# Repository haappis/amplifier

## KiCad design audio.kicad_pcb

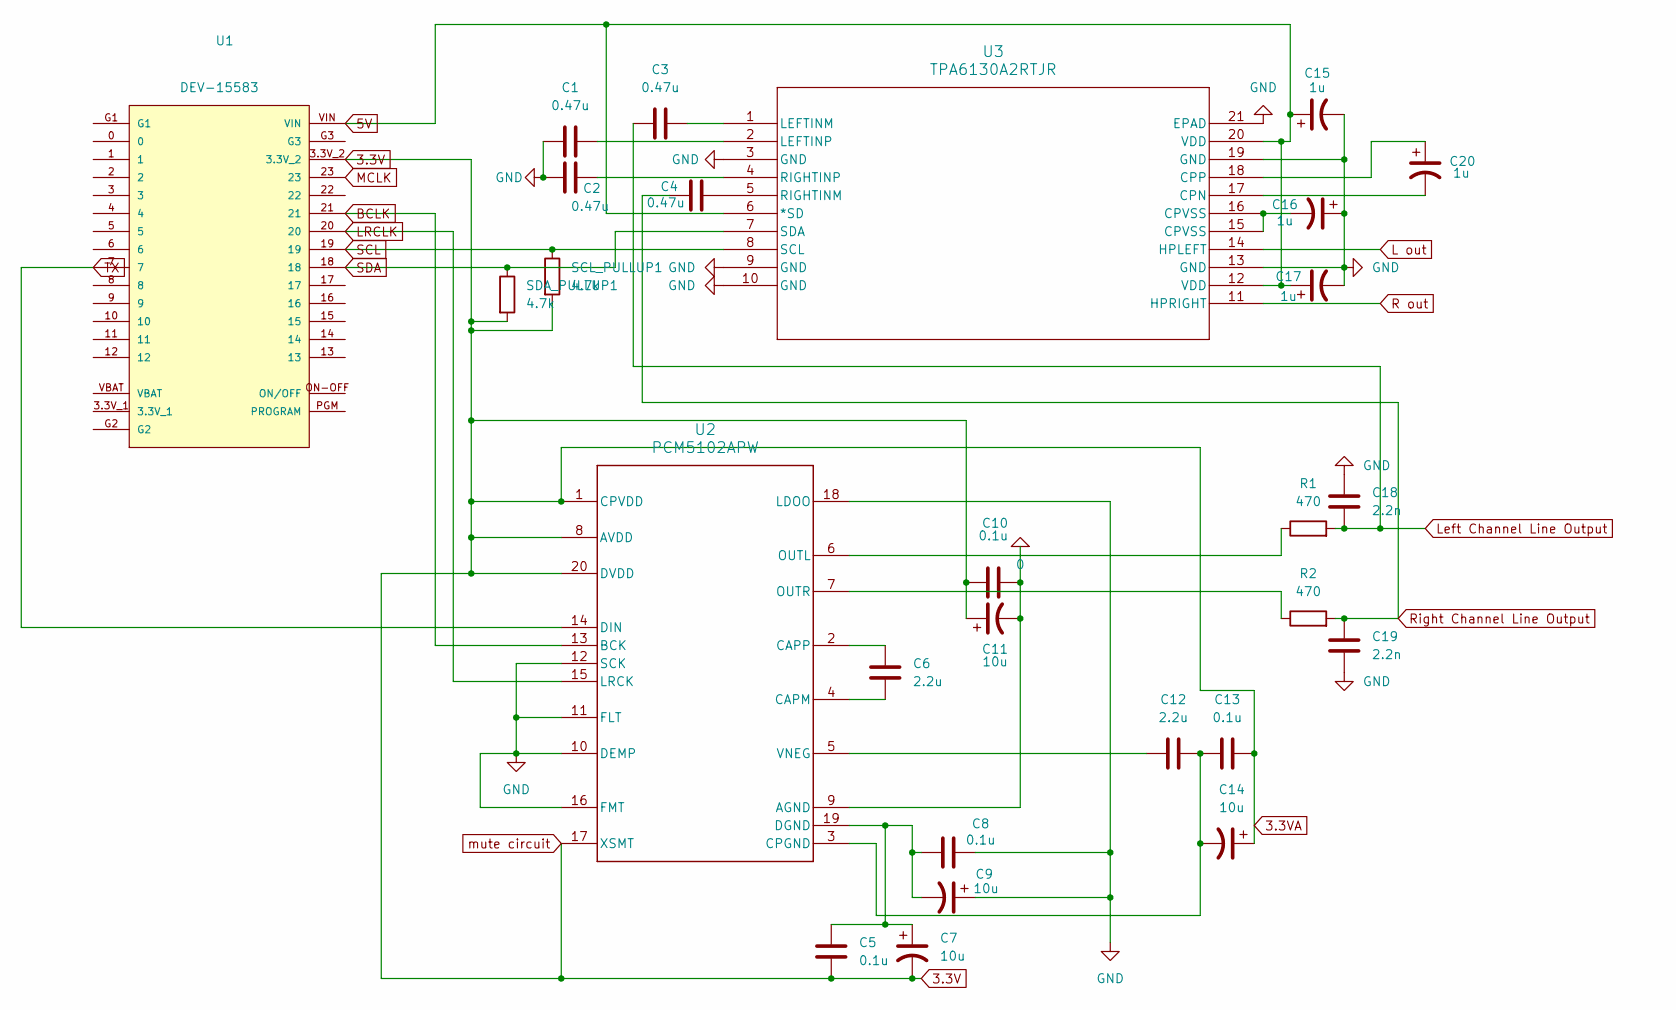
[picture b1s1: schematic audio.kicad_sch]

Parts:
C1, C2, C3, C4: 0.47u; C_0504_1310Metric
C5, C8, C10: 0.1u; C_0805_2012Metric
C6, C12: 2.2u; C_0504_1310Metric
C7, C9, C11: 10u; C_0805_2012Metric
C13: 0.1u; C_0504_1310Metric
C14: 10u; C_0504_1310Metric
C15, C16, C17, C20: 1u; C_0504_1310Metric
C18, C19: 2.2n; C_0504_1310Metric
R1, R2: 470; R_0805_2012Metric
SCL_PULLUP1: 4.7k; R_0805_2012Metric
SDA_PULLUP1: 4.7k; R_0805_2012Metric
U1: DEV-15583; MODULE_DEV-15583
U2: PCM5102APW; PW0020A_N
U3: TPA6130A2RTJR; RTJ20_2P7X2P7

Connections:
3.3V: C5.2, C7.2, C10.1, C11.1, C13.2, C14.1, SCL_PULLUP1.2, SDA_PULLUP1.2, U1.3.3V_2, U2.1 (CPVDD), U2.8 (AVDD), U2.17 (XSMT), U2.20 (DVDD); also elsewhere on the board
5V: C15.1, C17.1, U1.VIN, U3.6 (*SD), U3.12 (VDD), U3.20 (VDD); also elsewhere on the board
BCLK: U1.21, U2.13 (BCK); also elsewhere on the board
L out: U3.14 (HPLEFT); also elsewhere on the board
LRCLK: U1.20, U2.15 (LRCK); also elsewhere on the board
Left Channel Line Output: C3.1, C18.2, R1.2
unnamed: C16.2, U3.15 (CPVSS), U3.16 (CPVSS)
unnamed: C6.2, U2.4 (CAPM)
unnamed: C6.1, U2.2 (CAPP)
unnamed: C12.2, C13.1, C14.2, U2.3 (CPGND)
unnamed: C5.1, C7.1, C8.1, C9.2, U2.19 (DGND)
unnamed: R1.1, U2.6 (OUTL)
unnamed: R2.1, U2.7 (OUTR)
unnamed: C12.1, U2.5 (VNEG)
unnamed: C20.2, U3.17 (CPN)
unnamed: C20.1, U3.18 (CPP)
unnamed: C3.2, U3.1 (LEFTINM)
unnamed: C1.2, U3.2 (LEFTINP)
unnamed: C4.2, U3.5 (RIGHTINM)
unnamed: C2.2, U3.4 (RIGHTINP)
R out: U3.11 (HPRIGHT); also elsewhere on the board
Right Channel Line Output: C4.1, C19.1, R2.2
SCL: SCL_PULLUP1.1, U1.19, U3.8 (SCL); also elsewhere on the board
SDA: SDA_PULLUP1.1, U1.18, U3.7 (SDA); also elsewhere on the board
TX: U1.7, U2.14 (DIN); also elsewhere on the board

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
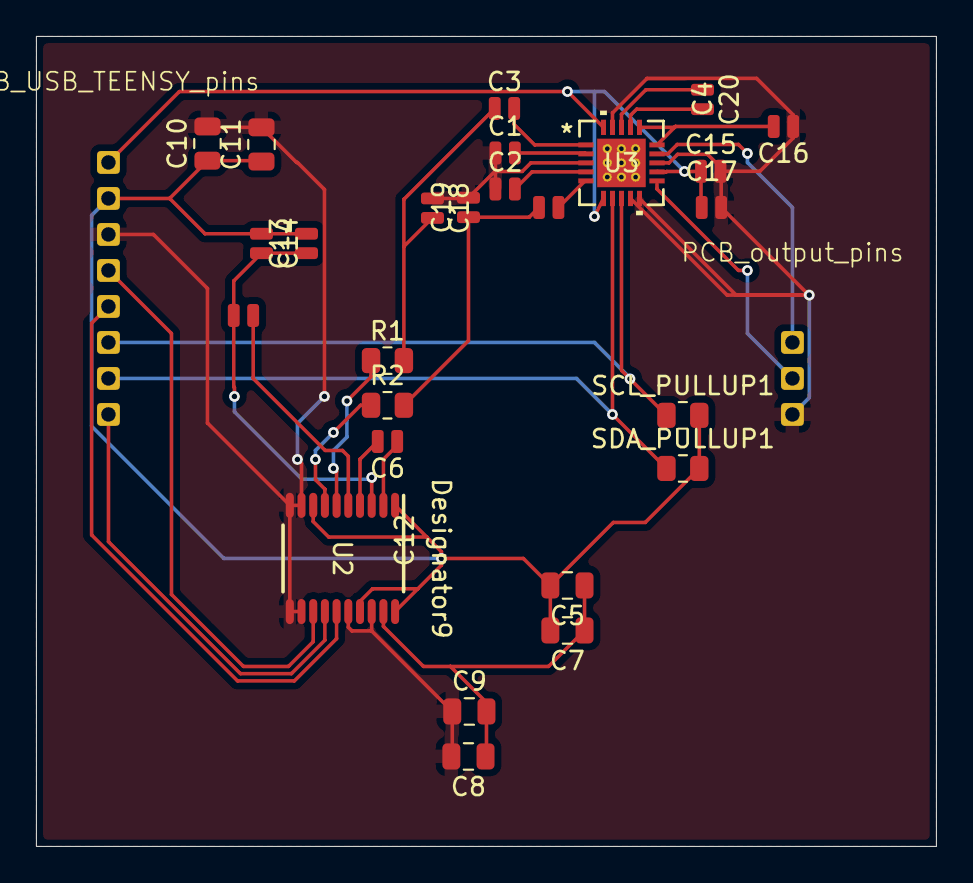
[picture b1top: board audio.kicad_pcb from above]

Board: 2 copper layers, 50.0 x 45.0 mm, 28 parts (0 on the bottom side), 26 nets.

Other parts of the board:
PCB_USB_TEENSY_pins: PCB_USB_TEENSY_input_pins
PCB_output_pins: PCB_output_pins

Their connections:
3.3V: PCB_USB_TEENSY_pins.3.3V; also elsewhere on the board
5V: PCB_USB_TEENSY_pins.5V; also elsewhere on the board
BCLK: PCB_USB_TEENSY_pins.BCLK; also elsewhere on the board
L out: PCB_output_pins.LOUT; also elsewhere on the board
LRCLK: PCB_USB_TEENSY_pins.LRCLK; also elsewhere on the board
R out: PCB_output_pins.ROUT; also elsewhere on the board
SCL: PCB_USB_TEENSY_pins.SCL; also elsewhere on the board
SDA: PCB_USB_TEENSY_pins.SDA; also elsewhere on the board
TX: PCB_USB_TEENSY_pins.DIN; also elsewhere on the board
